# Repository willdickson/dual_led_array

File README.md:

# dual_led_array 
PCB with dual arrays of IR and 628nm crimson leds. Arrays are 10x10 and 9x9 respectively. 

* [Bill-of-materials](BOM.txt)

# 3D View

# License: 
Creative Commons Attribution 4.0 International CC BY 4.0

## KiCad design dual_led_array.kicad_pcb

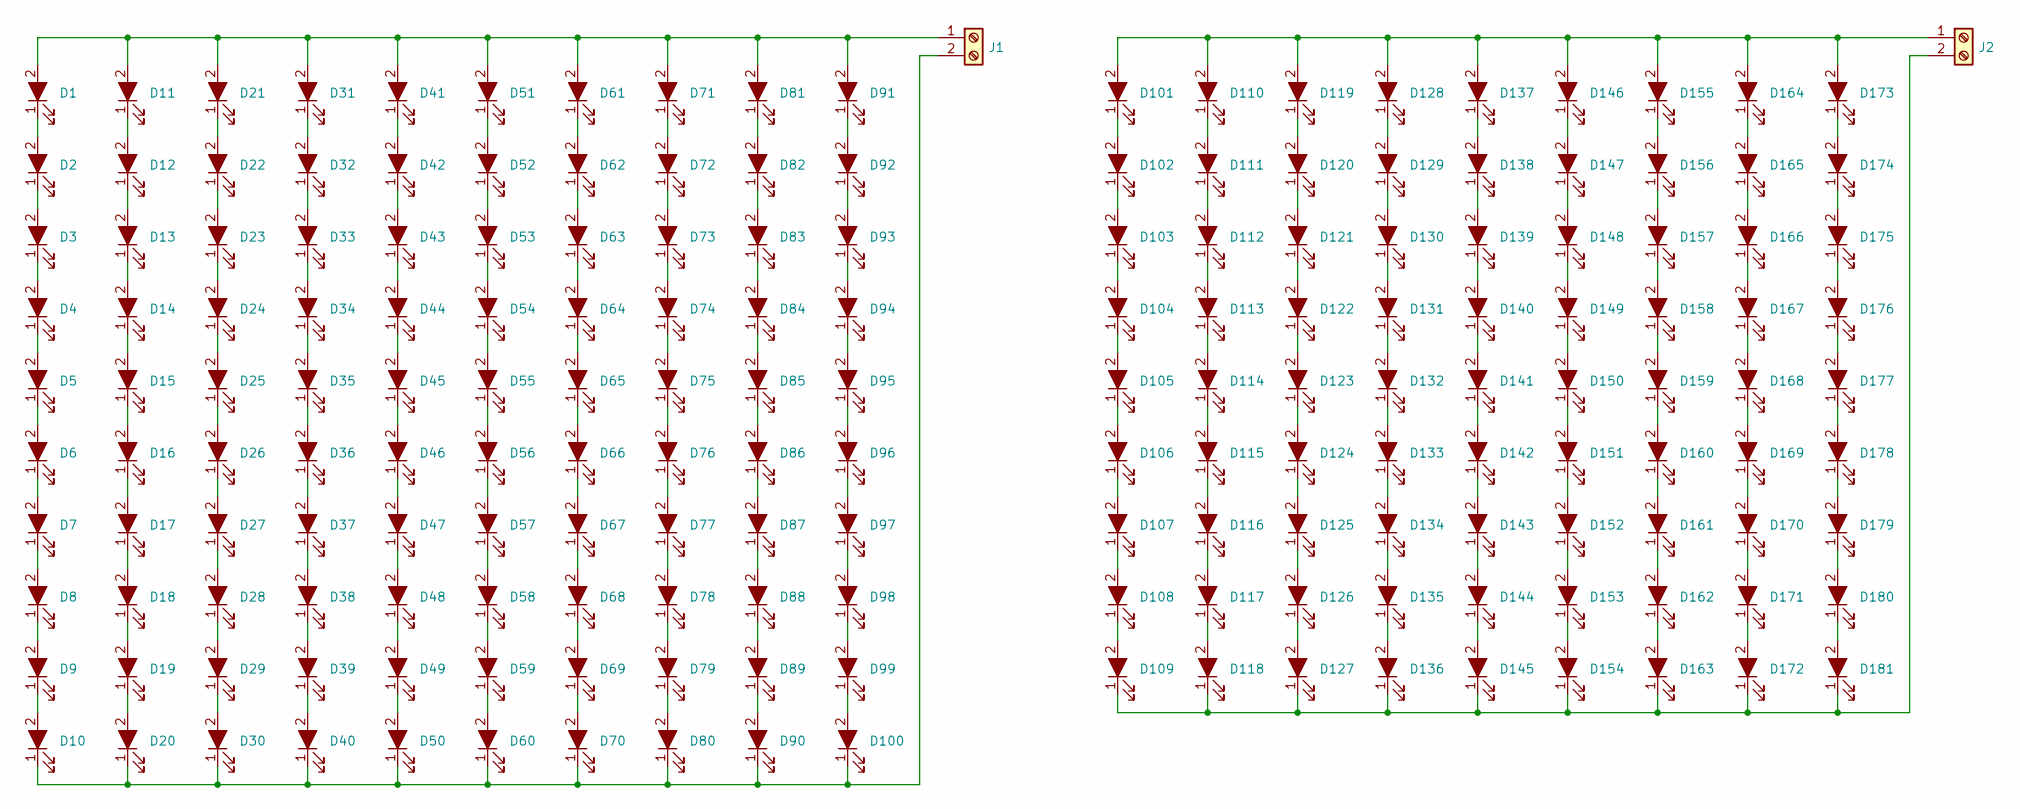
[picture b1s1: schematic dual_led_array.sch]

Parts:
D1, D2, D3, D4, D5, D6, D7, D8, D9, D10, D11, D12, D13, D14, D15, D16, D17, D18, D19, D20, D21, D22, D23, D24, D25, D26, D27, D28, D29, D30, D31, D32, D33, D34, D35, D36, D37, D38, D39, D40, D41, D42, D43, D44, D45, D46, D47, D48, D49, D50, D51, D52, D53, D54, D55, D56, D57, D58, D59, D60, D61, D62, D63, D64, D65, D66, D67, D68, D69, D70, D71, D72, D73, D74, D75, D76, D77, D78, D79, D80, D81, D82, D83, D84, D85, D86, D87, D88, D89, D90, D91, D92, D93, D94, D95, D96, D97, D98, D99, D100: LED_ALT; LED_5mm_custom
D101, D102, D103, D104, D105, D106, D107, D108, D109, D110, D111, D112, D113, D114, D115, D116, D117, D118, D119, D120, D121, D122, D123, D124, D125, D126, D127, D128, D129, D130, D131, D132, D133, D134, D135, D136, D137, D138, D139, D140, D141, D142, D143, D144, D145, D146, D147, D148, D149, D150, D151, D152, D153, D154, D155, D156, D157, D158, D159, D160, D161, D162, D163, D164, D165, D166, D167, D168, D169, D170, D171, D172, D173, D174, D175, D176, D177, D178, D179, D180, D181: LED_ALT; LED-0p2in
J1, J2: Screw_Terminal_01x02; BLOCK_CONN_2X1

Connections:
unnamed: D1.1 (K), D2.2 (A)
unnamed: D1.2 (A), D11.2 (A), D21.2 (A), D31.2 (A), D41.2 (A), D51.2 (A), D61.2 (A), D71.2 (A), D81.2 (A), D91.2 (A), J1.1
unnamed: D2.1 (K), D3.2 (A)
unnamed: D3.1 (K), D4.2 (A)
unnamed: D4.1 (K), D5.2 (A)
unnamed: D5.1 (K), D6.2 (A)
unnamed: D6.1 (K), D7.2 (A)
unnamed: D7.1 (K), D8.2 (A)
unnamed: D8.1 (K), D9.2 (A)
unnamed: D10.1 (K), D20.1 (K), D30.1 (K), D40.1 (K), D50.1 (K), D60.1 (K), D70.1 (K), D80.1 (K), D90.1 (K), D100.1 (K), J1.2
unnamed: D9.1 (K), D10.2 (A)
unnamed: D11.1 (K), D12.2 (A)
unnamed: D12.1 (K), D13.2 (A)
unnamed: D13.1 (K), D14.2 (A)
unnamed: D14.1 (K), D15.2 (A)
unnamed: D15.1 (K), D16.2 (A)
unnamed: D16.1 (K), D17.2 (A)
unnamed: D17.1 (K), D18.2 (A)
unnamed: D18.1 (K), D19.2 (A)
unnamed: D19.1 (K), D20.2 (A)
unnamed: D21.1 (K), D22.2 (A)
unnamed: D22.1 (K), D23.2 (A)
unnamed: D23.1 (K), D24.2 (A)
unnamed: D24.1 (K), D25.2 (A)
unnamed: D25.1 (K), D26.2 (A)
unnamed: D26.1 (K), D27.2 (A)
unnamed: D27.1 (K), D28.2 (A)
unnamed: D28.1 (K), D29.2 (A)
unnamed: D29.1 (K), D30.2 (A)
unnamed: D31.1 (K), D32.2 (A)
unnamed: D32.1 (K), D33.2 (A)
unnamed: D33.1 (K), D34.2 (A)
unnamed: D34.1 (K), D35.2 (A)
unnamed: D35.1 (K), D36.2 (A)
unnamed: D36.1 (K), D37.2 (A)
unnamed: D37.1 (K), D38.2 (A)
unnamed: D38.1 (K), D39.2 (A)
unnamed: D39.1 (K), D40.2 (A)
unnamed: D41.1 (K), D42.2 (A)
unnamed: D42.1 (K), D43.2 (A)
unnamed: D43.1 (K), D44.2 (A)
unnamed: D44.1 (K), D45.2 (A)
unnamed: D45.1 (K), D46.2 (A)
unnamed: D46.1 (K), D47.2 (A)
unnamed: D47.1 (K), D48.2 (A)
unnamed: D48.1 (K), D49.2 (A)
unnamed: D49.1 (K), D50.2 (A)
unnamed: D51.1 (K), D52.2 (A)
unnamed: D52.1 (K), D53.2 (A)
unnamed: D53.1 (K), D54.2 (A)
unnamed: D54.1 (K), D55.2 (A)
unnamed: D55.1 (K), D56.2 (A)
unnamed: D56.1 (K), D57.2 (A)
unnamed: D57.1 (K), D58.2 (A)
unnamed: D58.1 (K), D59.2 (A)
unnamed: D59.1 (K), D60.2 (A)
unnamed: D61.1 (K), D62.2 (A)
unnamed: D62.1 (K), D63.2 (A)
unnamed: D63.1 (K), D64.2 (A)
unnamed: D64.1 (K), D65.2 (A)
unnamed: D65.1 (K), D66.2 (A)
unnamed: D66.1 (K), D67.2 (A)
unnamed: D67.1 (K), D68.2 (A)
unnamed: D68.1 (K), D69.2 (A)
unnamed: D69.1 (K), D70.2 (A)
unnamed: D71.1 (K), D72.2 (A)
unnamed: D72.1 (K), D73.2 (A)
unnamed: D73.1 (K), D74.2 (A)
unnamed: D74.1 (K), D75.2 (A)
unnamed: D75.1 (K), D76.2 (A)
unnamed: D76.1 (K), D77.2 (A)
unnamed: D77.1 (K), D78.2 (A)
unnamed: D78.1 (K), D79.2 (A)
unnamed: D79.1 (K), D80.2 (A)
unnamed: D81.1 (K), D82.2 (A)
unnamed: D82.1 (K), D83.2 (A)
unnamed: D83.1 (K), D84.2 (A)
unnamed: D84.1 (K), D85.2 (A)
unnamed: D85.1 (K), D86.2 (A)
unnamed: D86.1 (K), D87.2 (A)
unnamed: D87.1 (K), D88.2 (A)
unnamed: D88.1 (K), D89.2 (A)
unnamed: D89.1 (K), D90.2 (A)
unnamed: D91.1 (K), D92.2 (A)
unnamed: D92.1 (K), D93.2 (A)
unnamed: D93.1 (K), D94.2 (A)
unnamed: D94.1 (K), D95.2 (A)
unnamed: D95.1 (K), D96.2 (A)
unnamed: D96.1 (K), D97.2 (A)
unnamed: D97.1 (K), D98.2 (A)
unnamed: D98.1 (K), D99.2 (A)
unnamed: D99.1 (K), D100.2 (A)
unnamed: D101.1 (K), D102.2 (A)
unnamed: D101.2 (A), D110.2 (A), D119.2 (A), D128.2 (A), D137.2 (A), D146.2 (A), D155.2 (A), D164.2 (A), D173.2 (A), J2.1
unnamed: D102.1 (K), D103.2 (A)
unnamed: D103.1 (K), D104.2 (A)
unnamed: D104.1 (K), D105.2 (A)
unnamed: D105.1 (K), D106.2 (A)
unnamed: D106.1 (K), D107.2 (A)
unnamed: D107.1 (K), D108.2 (A)
unnamed: D108.1 (K), D109.2 (A)
unnamed: D109.1 (K), D118.1 (K), D127.1 (K), D136.1 (K), D145.1 (K), D154.1 (K), D163.1 (K), D172.1 (K), D181.1 (K), J2.2
unnamed: D110.1 (K), D111.2 (A)
unnamed: D111.1 (K), D112.2 (A)
unnamed: D112.1 (K), D113.2 (A)
unnamed: D113.1 (K), D114.2 (A)
unnamed: D114.1 (K), D115.2 (A)
unnamed: D115.1 (K), D116.2 (A)
unnamed: D116.1 (K), D117.2 (A)
unnamed: D117.1 (K), D118.2 (A)
unnamed: D119.1 (K), D120.2 (A)
unnamed: D120.1 (K), D121.2 (A)
unnamed: D121.1 (K), D122.2 (A)
unnamed: D122.1 (K), D123.2 (A)
unnamed: D123.1 (K), D124.2 (A)
unnamed: D124.1 (K), D125.2 (A)
unnamed: D125.1 (K), D126.2 (A)
unnamed: D126.1 (K), D127.2 (A)
unnamed: D128.1 (K), D129.2 (A)
unnamed: D129.1 (K), D130.2 (A)
unnamed: D130.1 (K), D131.2 (A)
unnamed: D131.1 (K), D132.2 (A)
unnamed: D132.1 (K), D133.2 (A)
unnamed: D133.1 (K), D134.2 (A)
unnamed: D134.1 (K), D135.2 (A)
unnamed: D135.1 (K), D136.2 (A)
unnamed: D137.1 (K), D138.2 (A)
unnamed: D138.1 (K), D139.2 (A)
unnamed: D139.1 (K), D140.2 (A)
unnamed: D140.1 (K), D141.2 (A)
unnamed: D141.1 (K), D142.2 (A)
unnamed: D142.1 (K), D143.2 (A)
unnamed: D143.1 (K), D144.2 (A)
unnamed: D144.1 (K), D145.2 (A)
unnamed: D146.1 (K), D147.2 (A)
unnamed: D147.1 (K), D148.2 (A)
unnamed: D148.1 (K), D149.2 (A)
unnamed: D149.1 (K), D150.2 (A)
unnamed: D150.1 (K), D151.2 (A)
unnamed: D151.1 (K), D152.2 (A)
unnamed: D152.1 (K), D153.2 (A)
unnamed: D153.1 (K), D154.2 (A)
unnamed: D155.1 (K), D156.2 (A)
unnamed: D156.1 (K), D157.2 (A)
unnamed: D157.1 (K), D158.2 (A)
unnamed: D158.1 (K), D159.2 (A)
unnamed: D159.1 (K), D160.2 (A)
unnamed: D160.1 (K), D161.2 (A)
unnamed: D161.1 (K), D162.2 (A)
unnamed: D162.1 (K), D163.2 (A)
unnamed: D164.1 (K), D165.2 (A)
unnamed: D165.1 (K), D166.2 (A)
unnamed: D166.1 (K), D167.2 (A)
unnamed: D167.1 (K), D168.2 (A)
unnamed: D168.1 (K), D169.2 (A)
unnamed: D169.1 (K), D170.2 (A)
unnamed: D170.1 (K), D171.2 (A)
unnamed: D171.1 (K), D172.2 (A)
unnamed: D173.1 (K), D174.2 (A)
unnamed: D174.1 (K), D175.2 (A)
unnamed: D175.1 (K), D176.2 (A)
unnamed: D176.1 (K), D177.2 (A)
unnamed: D177.1 (K), D178.2 (A)
unnamed: D178.1 (K), D179.2 (A)
unnamed: D179.1 (K), D180.2 (A)
unnamed: D180.1 (K), D181.2 (A)

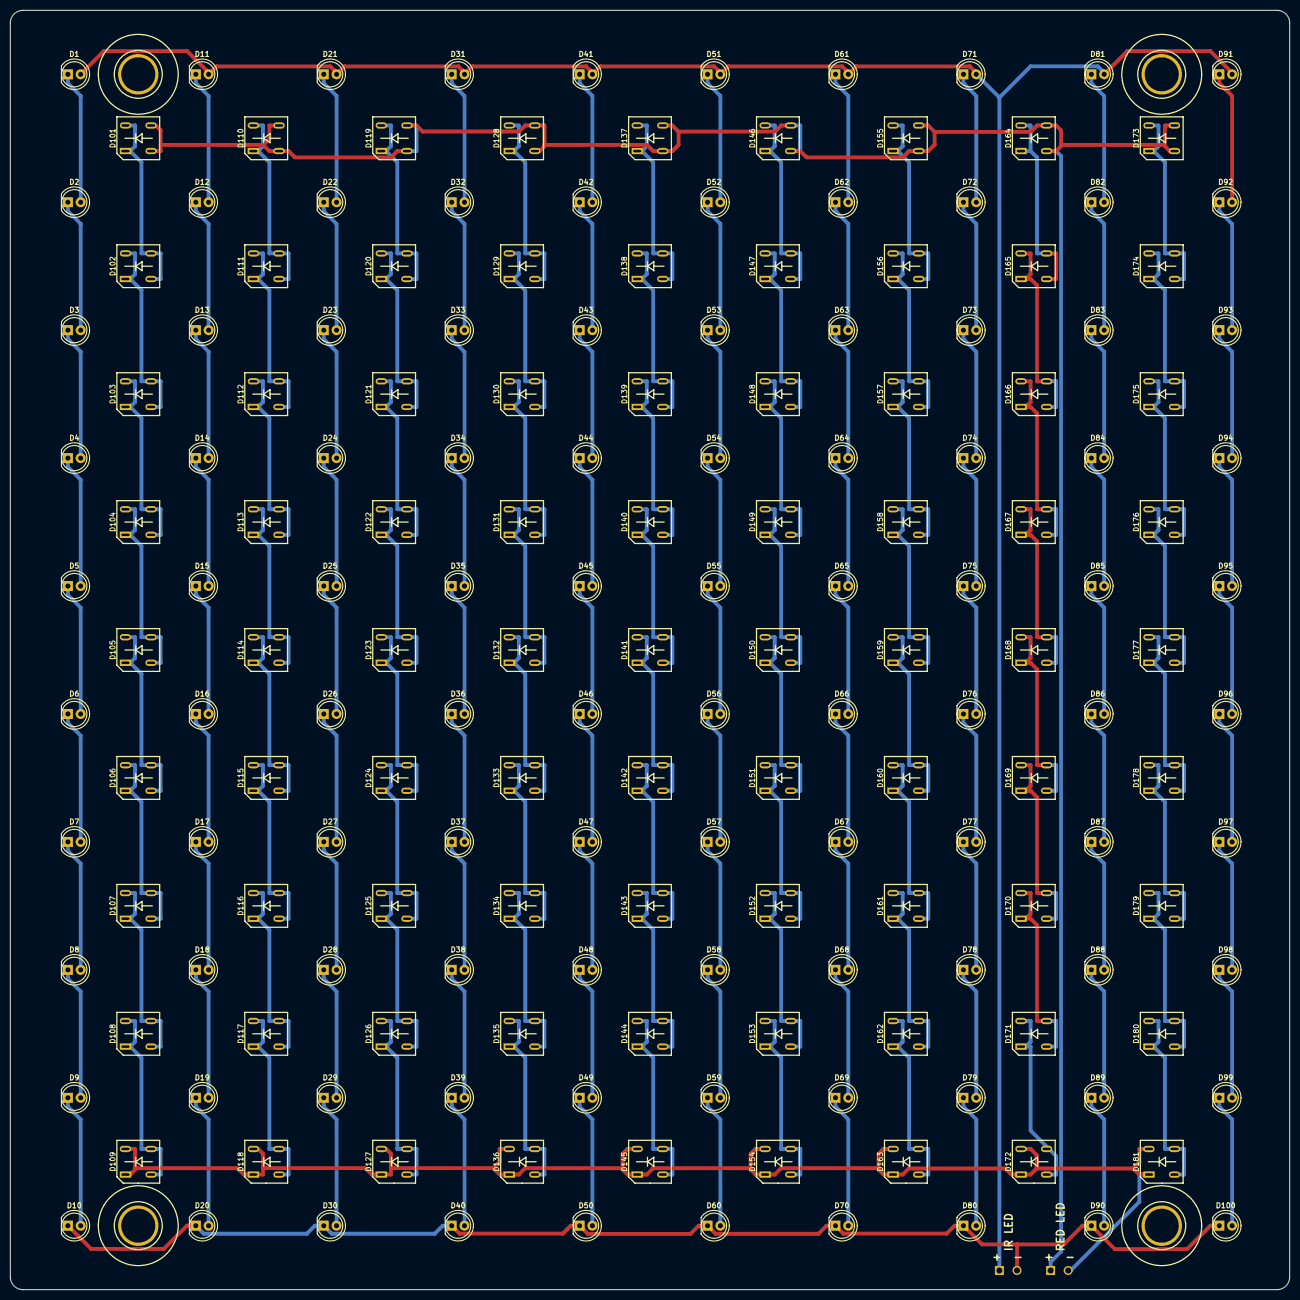
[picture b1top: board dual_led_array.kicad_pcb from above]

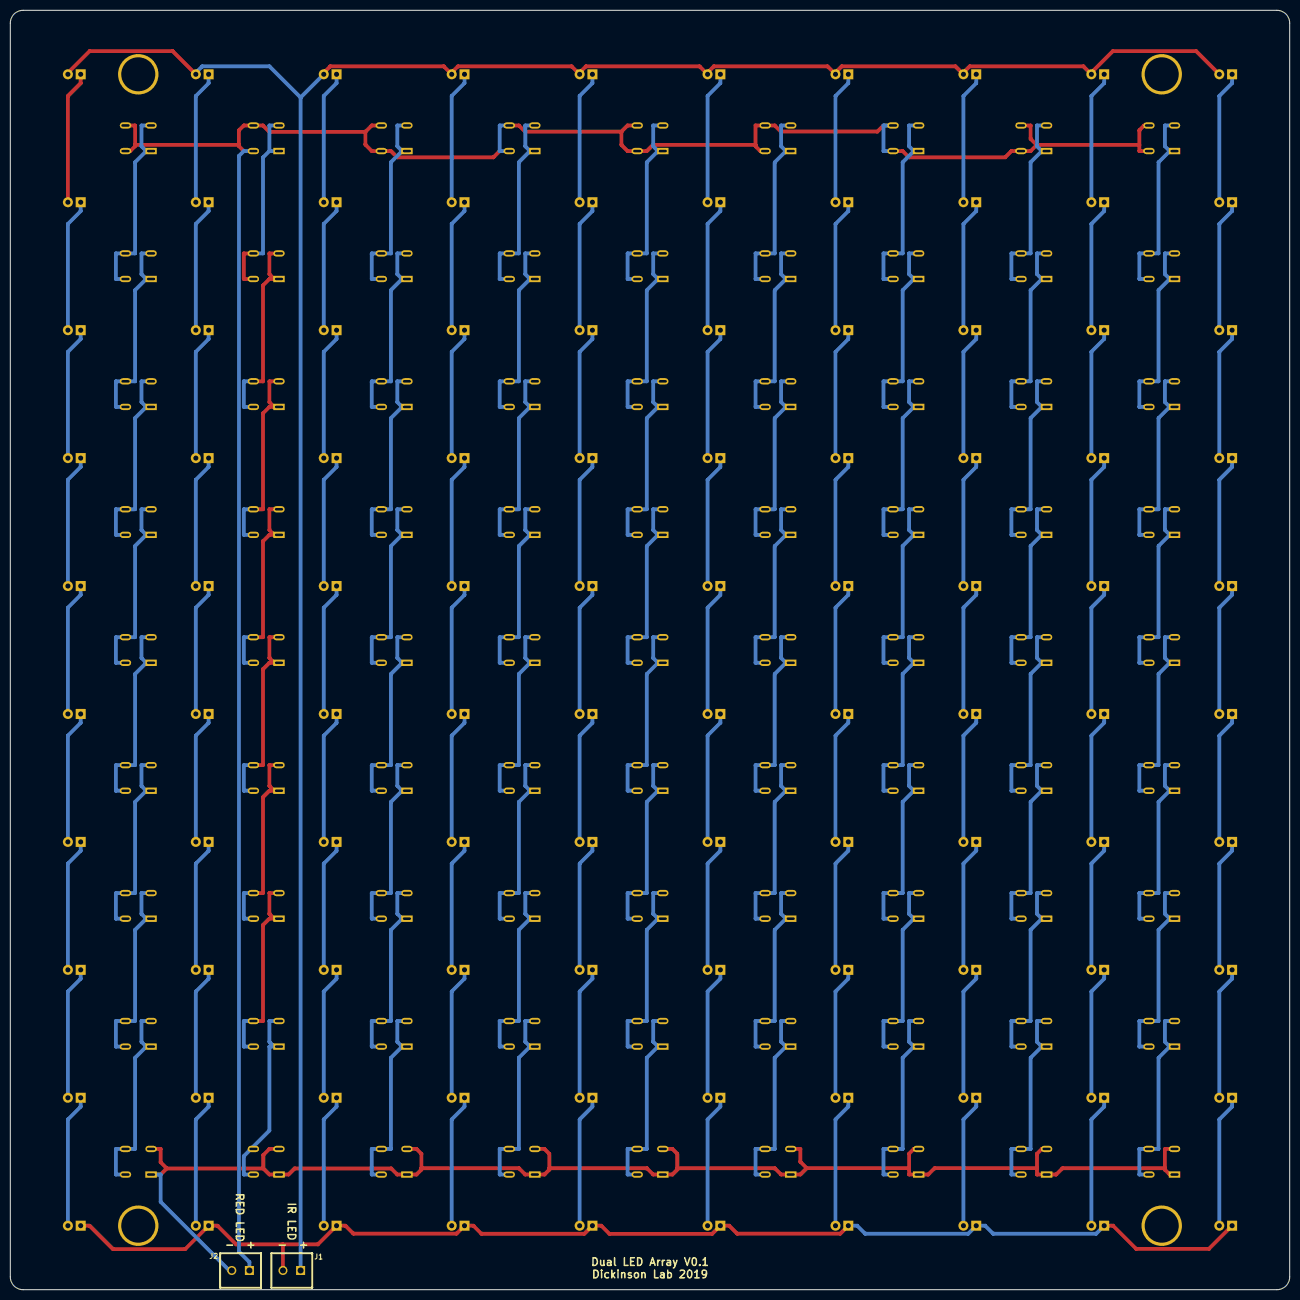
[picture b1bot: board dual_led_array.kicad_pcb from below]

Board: 2 copper layers, 254.0 x 254.0 mm, 187 parts (2 on the bottom side), 166 nets.

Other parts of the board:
M1, M2, M3, M4: quarter_twenty

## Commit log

2019-10-19 Project creation.
2019-10-19 Edited readme.
2019-10-21 Added annotations to PCB.
2019-10-21 Added gerber files for version 0.1.
2019-10-21 Added .zip archive of V0.1 gerber files for easy ordering.
2019-10-30 Added BOM.
2020-07-04 Added alternative LED to the BOM.
